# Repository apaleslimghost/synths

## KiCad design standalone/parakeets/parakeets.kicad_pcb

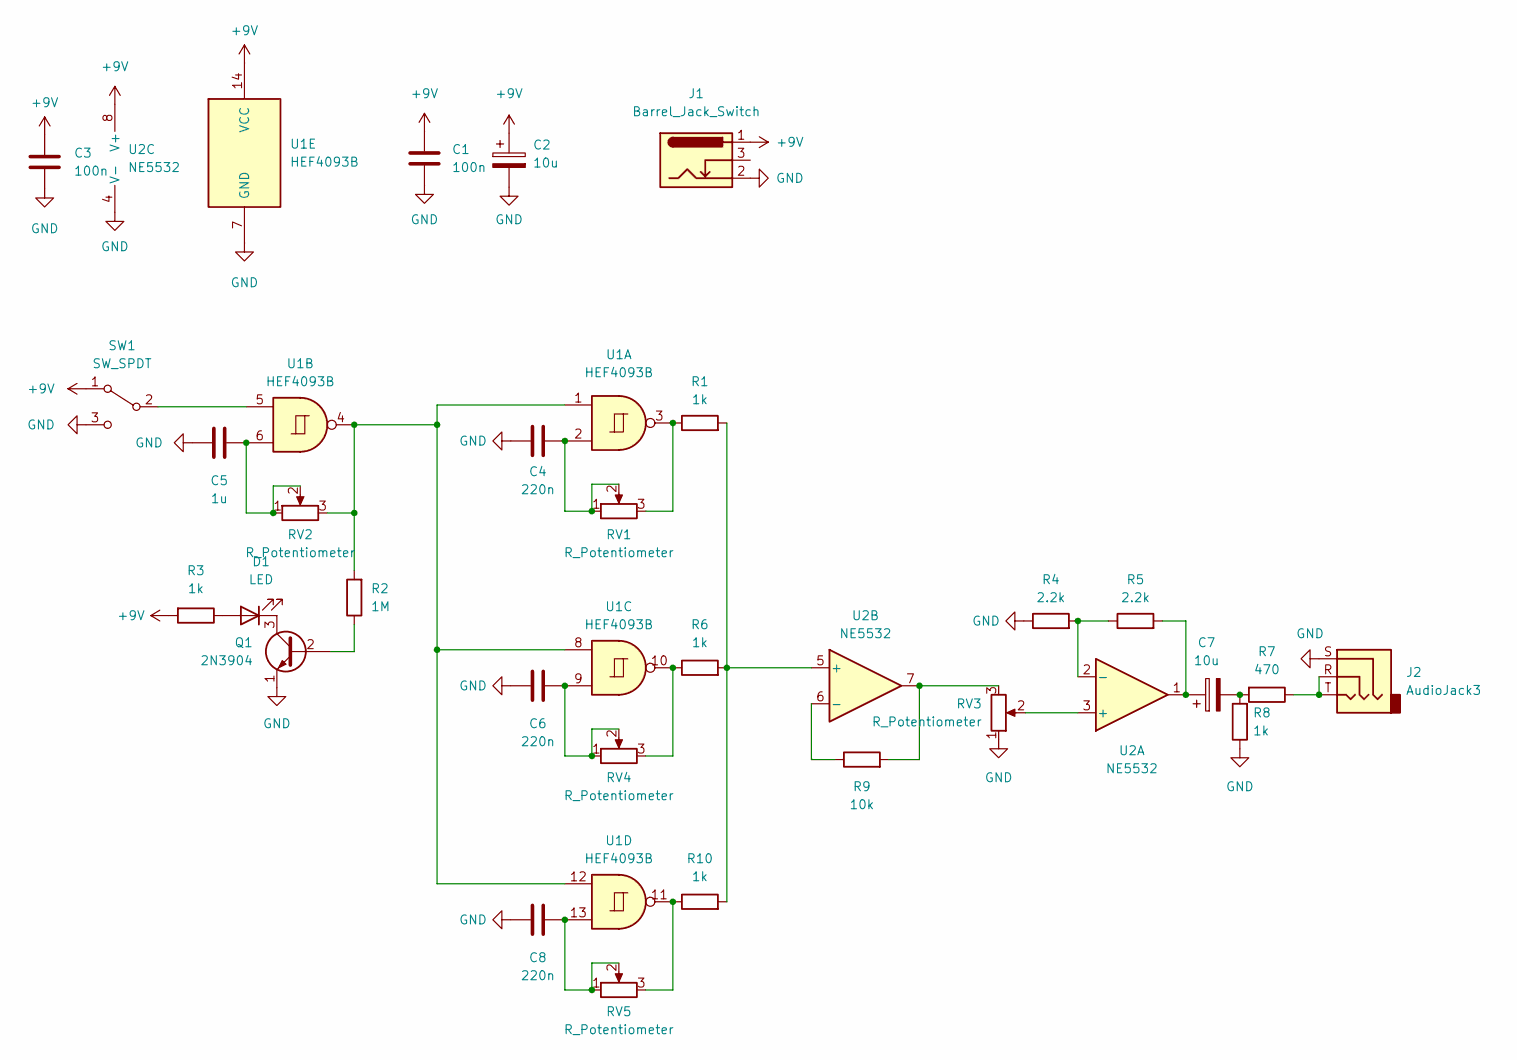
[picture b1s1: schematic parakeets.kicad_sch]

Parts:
C1, C3: 100n; C_Disc_D4.3mm_W1.9mm_P5.00mm
C2, C7: 10u; CP_Radial_D5.0mm_P2.50mm
C4, C6, C8: 220n; C_Rect_L7.0mm_W3.5mm_P5.00mm
C5: 1u; C_Rect_L7.0mm_W6.5mm_P5.00mm
D1: LED; LED_D3.0mm
J1: Barrel_Jack_Switch; CUI_PJ-202A
J2: AudioJack3; Jack_3.5mm_QingPu_WQP-PJ366ST_Vertical
Q1: 2N3904; TO-92_Inline_Wide
R1, R6, R8, R10: 1k; R_Axial_DIN0207_L6.3mm_D2.5mm_P7.62mm_Horizontal
R2: 1M; R_Axial_DIN0207_L6.3mm_D2.5mm_P2.54mm_Vertical
R3: 1k; R_Axial_DIN0207_L6.3mm_D2.5mm_P2.54mm_Vertical
R4, R5: 2.2k; R_Axial_DIN0207_L6.3mm_D2.5mm_P7.62mm_Horizontal
R7: 470; R_Axial_DIN0207_L6.3mm_D2.5mm_P7.62mm_Horizontal
R9: 10k; R_Axial_DIN0207_L6.3mm_D2.5mm_P7.62mm_Horizontal
RV1, RV2, RV3, RV4, RV5: R_Potentiometer; Potentiometer_Alpha_RD901F-40-00D_Single_Vertical
SW1: SW_SPDT; Sub Mini Toggle Switch SPDT
U1: HEF4093B; DIP-14_W7.62mm
U2: NE5532; DIP-8_W7.62mm

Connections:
+9V: C1.1, C2.1, C3.1, J1.1, R3.2, SW1.1 (A), U1.14 (VCC), U2.8 (V+)
GND: C1.2, C2.2, C3.2, C4.2, C5.2, C6.2, C8.2, J1.2, J2.S, Q1.1 (E), R4.1, R8.1, RV3.1, SW1.3 (C), U1.7 (GND), U2.4 (V-)
unnamed: C4.1, RV1.1, RV1.2, U1.2
unnamed: C5.1, RV2.1, RV2.2, U1.6
unnamed: C6.1, RV4.1, RV4.2, U1.9
unnamed: C7.1, R5.2, U2.1
unnamed: C7.2, R7.2, R8.2
unnamed: C8.1, RV5.1, RV5.2, U1.13
unnamed: D1.1 (K), Q1.3 (C)
unnamed: D1.2 (A), R3.1
unnamed: J2.R, J2.T, R7.1
unnamed: Q1.2 (B), R2.1
unnamed: R1.1, RV1.3, U1.3
unnamed: R1.2, R6.2, R10.2, U2.5 (+)
unnamed: R2.2, RV2.3, U1.1, U1.4, U1.8, U1.12
unnamed: R4.2, R5.1, U2.2 (-)
unnamed: R6.1, RV4.3, U1.10
unnamed: R9.1, U2.6 (-)
unnamed: R9.2, RV3.3, U2.7
unnamed: R10.1, RV5.3, U1.11
unnamed: RV3.2, U2.3 (+)
unnamed: SW1.2 (B), U1.5

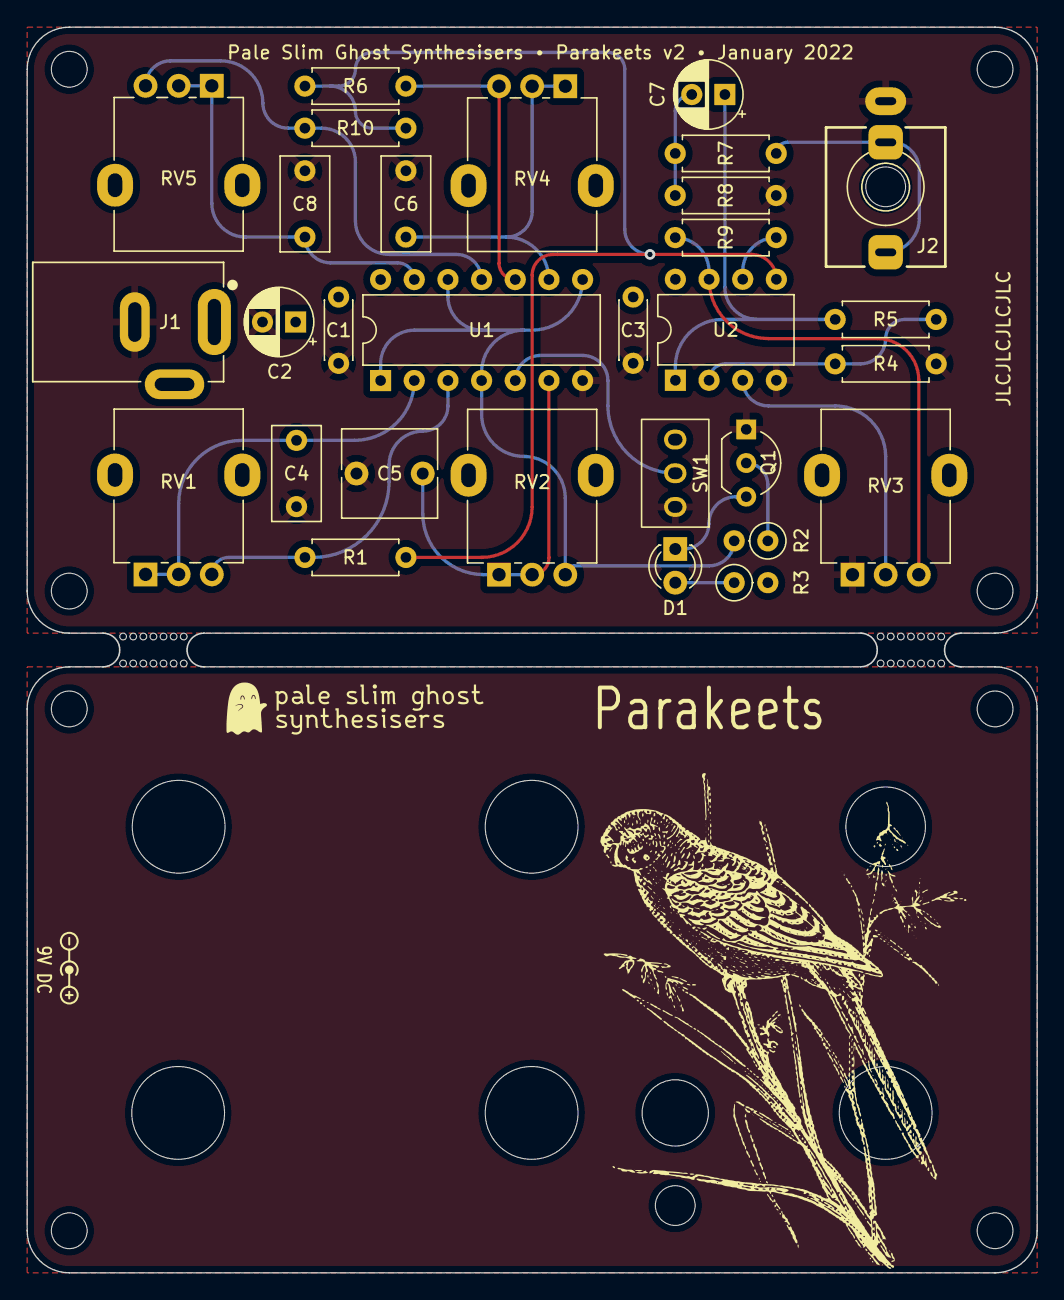
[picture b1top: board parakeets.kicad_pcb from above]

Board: 2 copper layers, 76.2 x 94.0 mm, 32 parts (0 on the bottom side), 22 nets.

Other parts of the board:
mouse-bite-2mm-slot, mouse-bite-2mm-slot#2: VAL**; mousebite-2.54x5.08mm

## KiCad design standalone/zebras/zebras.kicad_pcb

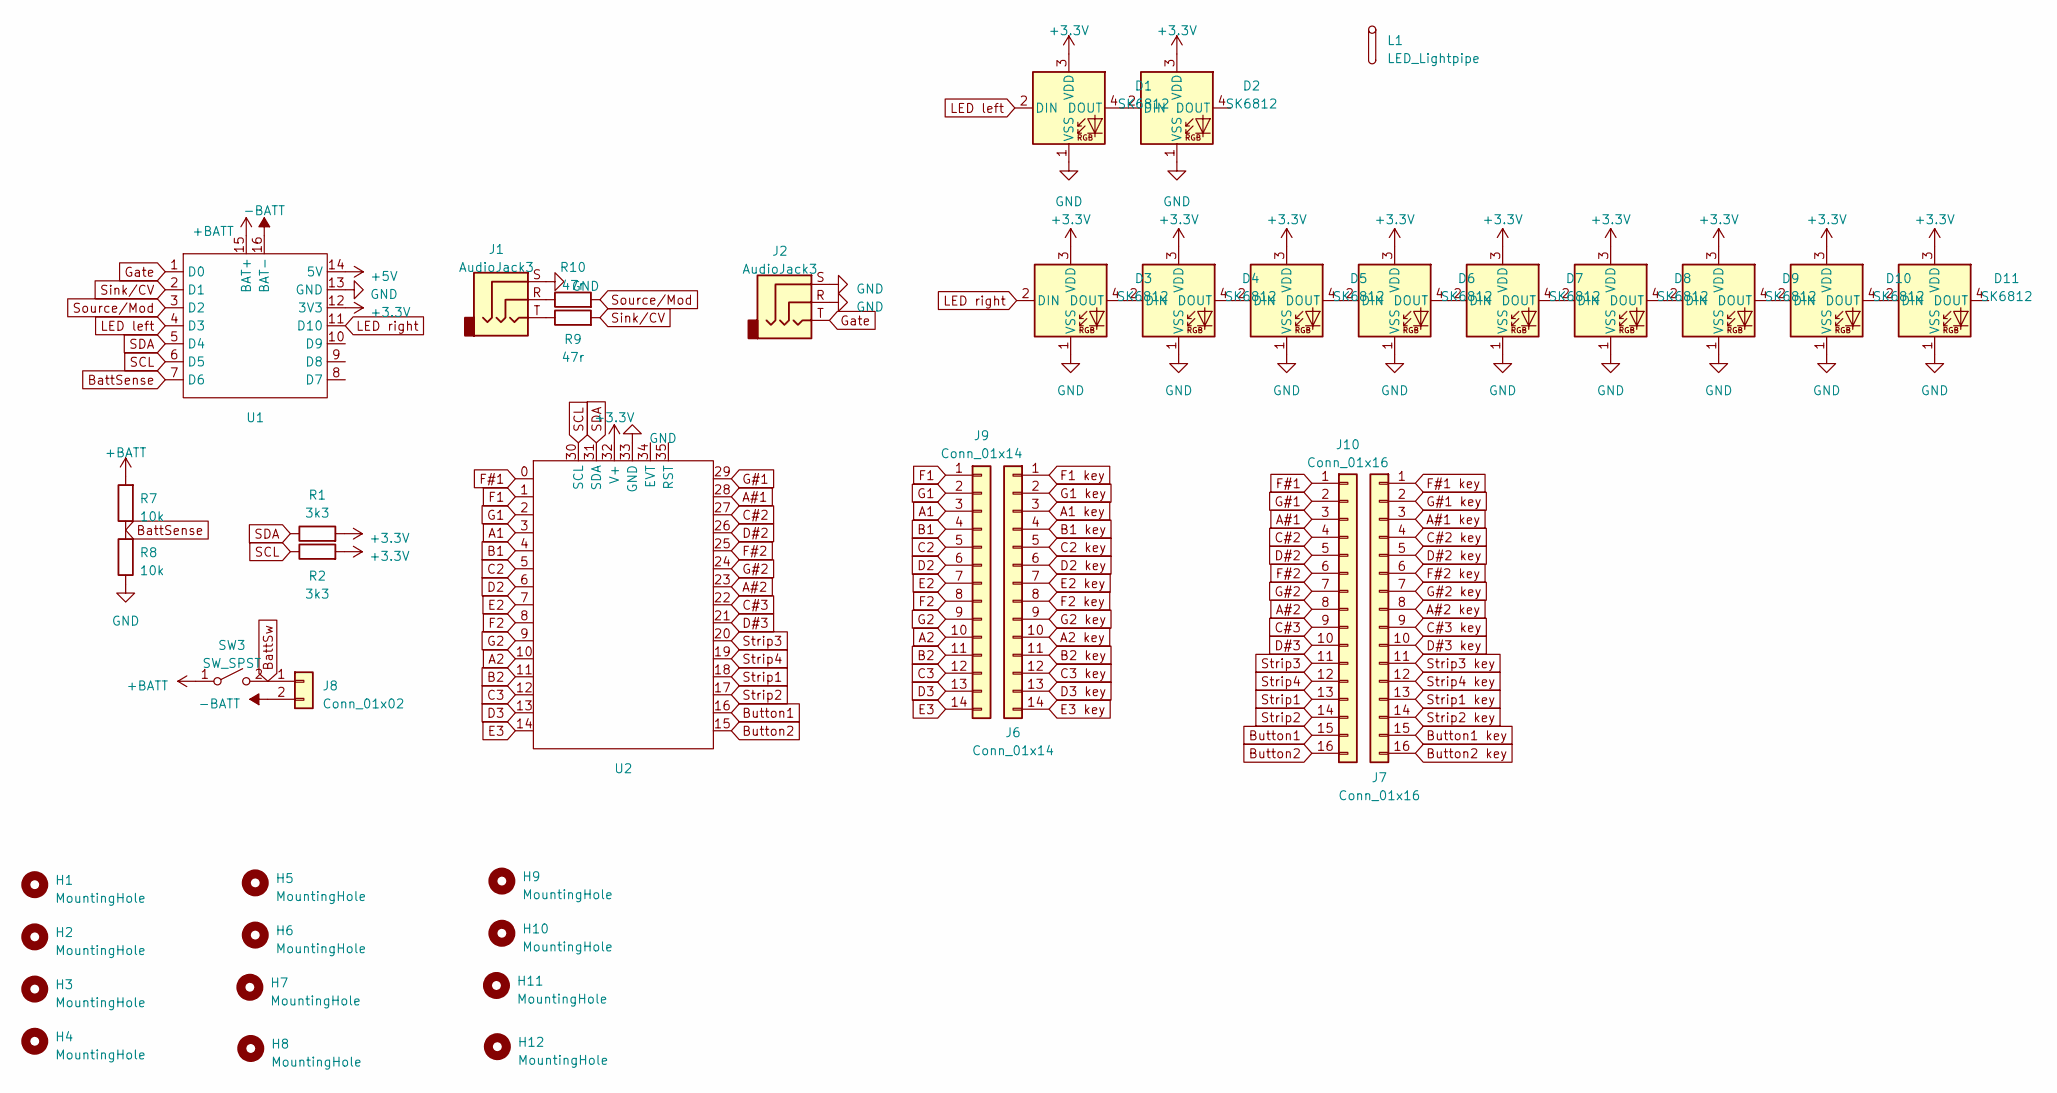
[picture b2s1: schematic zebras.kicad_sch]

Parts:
D1, D2, D3, D4, D5, D6, D7, D8, D9, D10, D11: SK6812; LED_SK6812_PLCC4_5.0x5.0mm_P3.2mm
H1, H2, H3, H4, H5, H6: MountingHole; M2.5 Standoff 6mm
H7, H8: MountingHole; M2.5 Standoff 4mm
H9, H10, H11, H12: MountingHole; MountingHole_2.7mm_M2.5
J1, J2: AudioJack3; Jack_3.5mm_CUI_SJ-3523-SMT_Horizontal
J6: Conn_01x14; PinHeader_2x07_P1.27mm_Vertical_SMD
J7: Conn_01x16; PinHeader_2x08_P1.27mm_Vertical_SMD
J8: Conn_01x02; JST_PH_S2B-PH-K_1x02_P2.00mm_Horizontal
J9: Conn_01x14; PinSocket_2x07_P1.27mm_Vertical_SMD
J10: Conn_01x16; PinSocket_2x08_P1.27mm_Vertical_SMD
L1: LED_Lightpipe; Zebras lightguide
R1, R2: 3k3; R_0805_2012Metric_Pad1.20x1.40mm_HandSolder
R7, R8: 10k; R_0805_2012Metric_Pad1.20x1.40mm_HandSolder
R9, R10: 47r; R_0805_2012Metric_Pad1.20x1.40mm_HandSolder
SW3: SW_SPST; EG1247
U1: SeeedXIAOBattery
U2: TrillCraft

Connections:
+3.3V: D1.3 (VDD), D2.3 (VDD), D3.3 (VDD), D4.3 (VDD), D5.3 (VDD), D6.3 (VDD), D7.3 (VDD), D8.3 (VDD), D9.3 (VDD), D10.3 (VDD), D11.3 (VDD), R1.2, R2.2, U1.12 (3V3), U2.32 (V+)
+5V: U1.14 (5V)
+BATT: R7.2, SW3.1 (A), U1.15 (BAT+)
-BATT: J8.2, U1.16 (BAT-)
A1: J9.3, U2.3
A1 key: J6.3
A2: J9.10, U2.10
A2 key: J6.10
A#1: J10.3, U2.28
A#1 key: J7.3
A#2: J10.8, U2.23
A#2 key: J7.8
B1: J9.4, U2.4
B1 key: J6.4
B2: J9.11, U2.11
B2 key: J6.11
BattSense: R7.1, R8.2, U1.7 (D6)
BattSw: J8.1, SW3.2 (B)
Button1: J10.15, U2.16
Button1 key: J7.15
Button2: J10.16, U2.15
Button2 key: J7.16
C2: J9.5, U2.5
C2 key: J6.5
C3: J9.12, U2.12
C3 key: J6.12
C#2: J10.4, U2.27
C#2 key: J7.4
C#3: J10.9, U2.22
C#3 key: J7.9
D2: J9.6, U2.6
D2 key: J6.6
D3: J9.13, U2.13
D3 key: J6.13
D#2: J10.5, U2.26
D#2 key: J7.5
D#3: J10.10, U2.21
D#3 key: J7.10
E2: J9.7, U2.7
E2 key: J6.7
E3: J9.14, U2.14
E3 key: J6.14
F1: J9.1, U2.1
F1 key: J6.1
F2: J9.8, U2.8
F2 key: J6.8
F#1: J10.1, U2.0
F#1 key: J7.1
F#2: J10.6, U2.25
F#2 key: J7.6
G1: J9.2, U2.2
G1 key: J6.2
G2: J9.9, U2.9
G2 key: J6.9
G#1: J10.2, U2.29
G#1 key: J7.2
G#2: J10.7, U2.24
G#2 key: J7.7
GND: D1.1 (VSS), D2.1 (VSS), D3.1 (VSS), D4.1 (VSS), D5.1 (VSS), D6.1 (VSS), D7.1 (VSS), D8.1 (VSS), D9.1 (VSS), D10.1 (VSS), D11.1 (VSS), J1.S, J2.R, J2.S, R8.1, U1.13 (GND), U2.33 (GND)
Gate: J2.T, U1.1 (D0)
LED left: D1.2 (DIN), U1.4 (D3)
LED right: D3.2 (DIN), U1.11 (D10)
unnamed: D1.4 (DOUT), D2.2 (DIN)
unnamed: D3.4 (DOUT), D4.2 (DIN)
unnamed: D4.4 (DOUT), D5.2 (DIN)
unnamed: D5.4 (DOUT), D6.2 (DIN)
unnamed: D6.4 (DOUT), D7.2 (DIN)
unnamed: D7.4 (DOUT), D8.2 (DIN)
unnamed: D8.4 (DOUT), D9.2 (DIN)
unnamed: D9.4 (DOUT), D10.2 (DIN)
unnamed: D10.4 (DOUT), D11.2 (DIN)
unnamed: J1.R, R10.1
unnamed: J1.T, R9.1
SCL: R2.1, U1.6 (D5), U2.30 (SCL)
SDA: R1.1, U1.5 (D4), U2.31 (SDA)
Sink/CV: R9.2, U1.2 (D1)
Source/Mod: R10.2, U1.3 (D2)
Strip1: J10.13, U2.18
Strip1 key: J7.13
Strip2: J10.14, U2.17
Strip2 key: J7.14
Strip3: J10.11, U2.20
Strip3 key: J7.11
Strip4: J10.12, U2.19
Strip4 key: J7.12

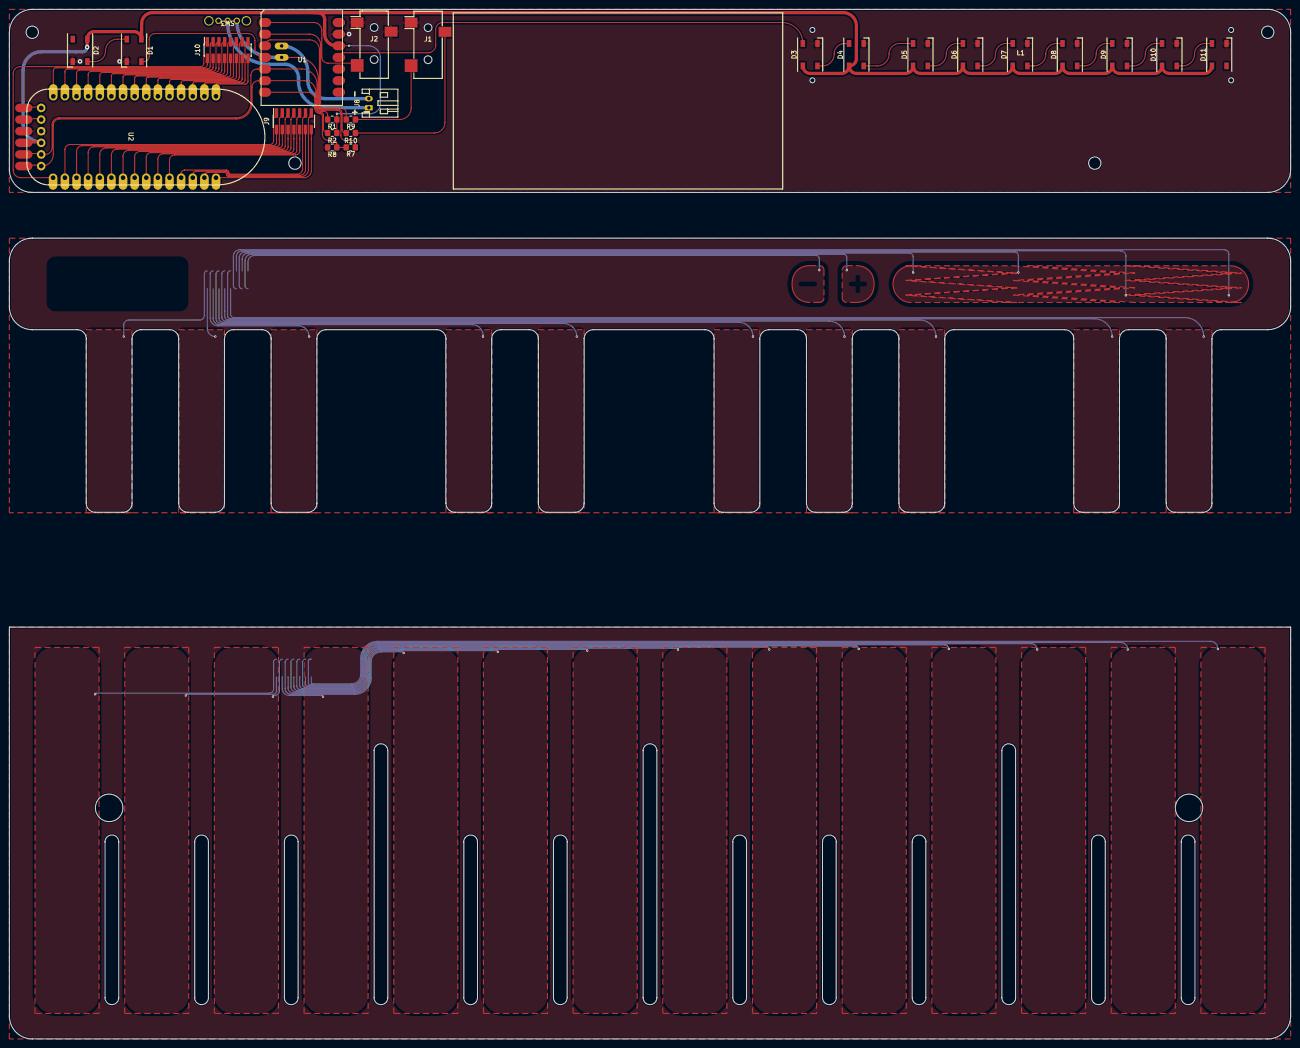
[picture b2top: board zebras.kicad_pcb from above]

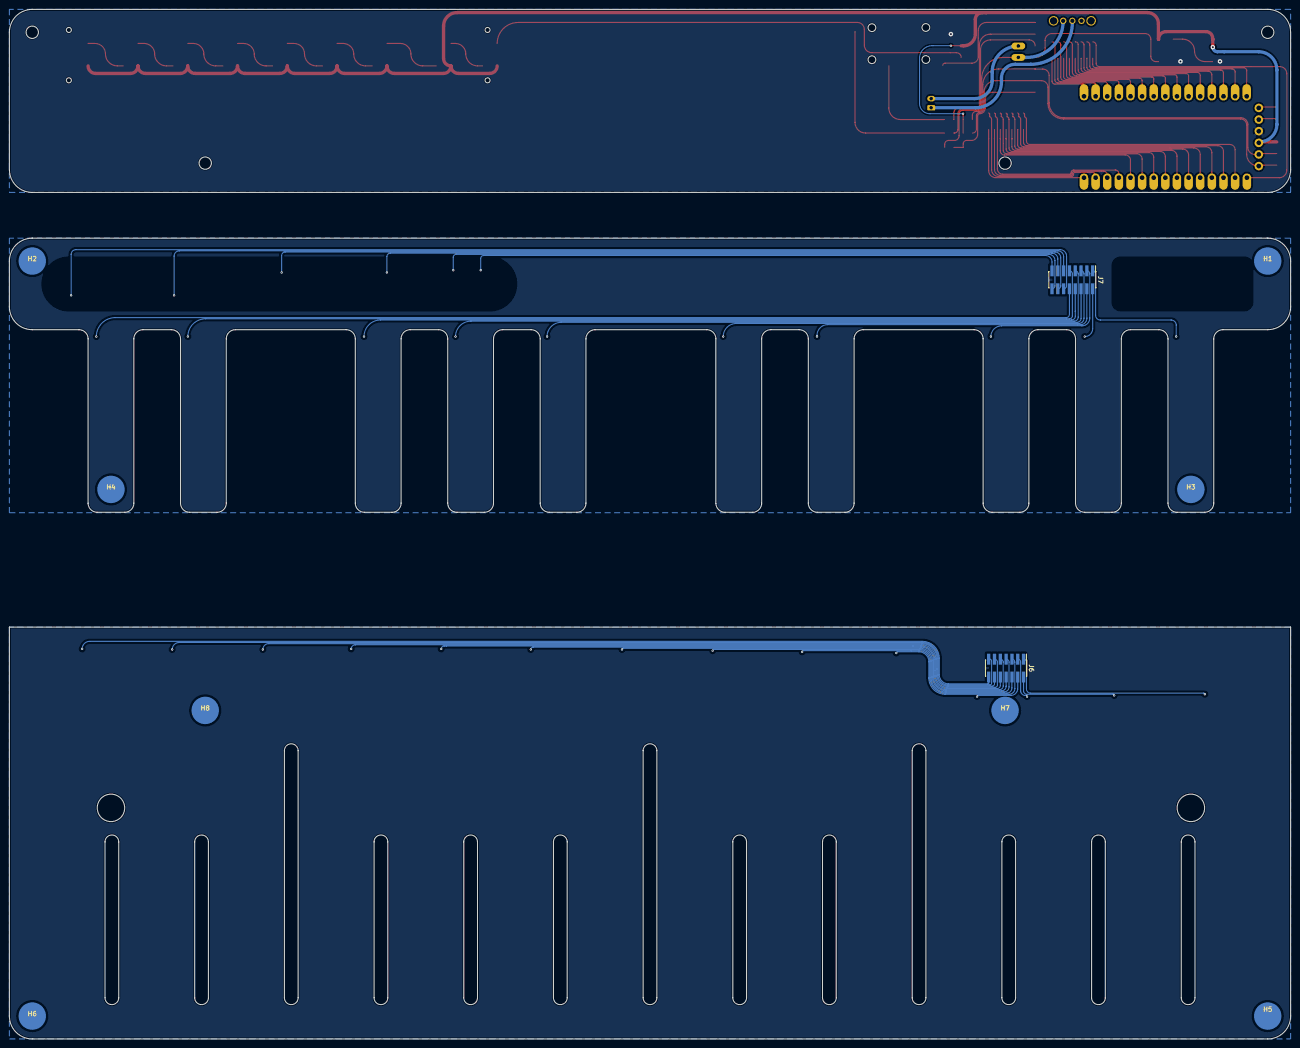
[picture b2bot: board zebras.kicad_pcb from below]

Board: 2 copper layers, 280.0 x 225.0 mm, 43 parts (10 on the bottom side), 54 nets.

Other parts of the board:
B1, B2, B3: Board
